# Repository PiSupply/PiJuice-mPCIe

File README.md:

# PiJuice-mPCIe
Resources for the PiJuice mPCIe board

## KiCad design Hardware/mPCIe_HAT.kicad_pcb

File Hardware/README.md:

# Hardware

EC25 datasheets - https://www.quectel.com/ProductDownload/EC25MiniPCIe.html

Change Log:

- V1.1_2021_12_30
    - Q2B connection fix
    - Position file generated

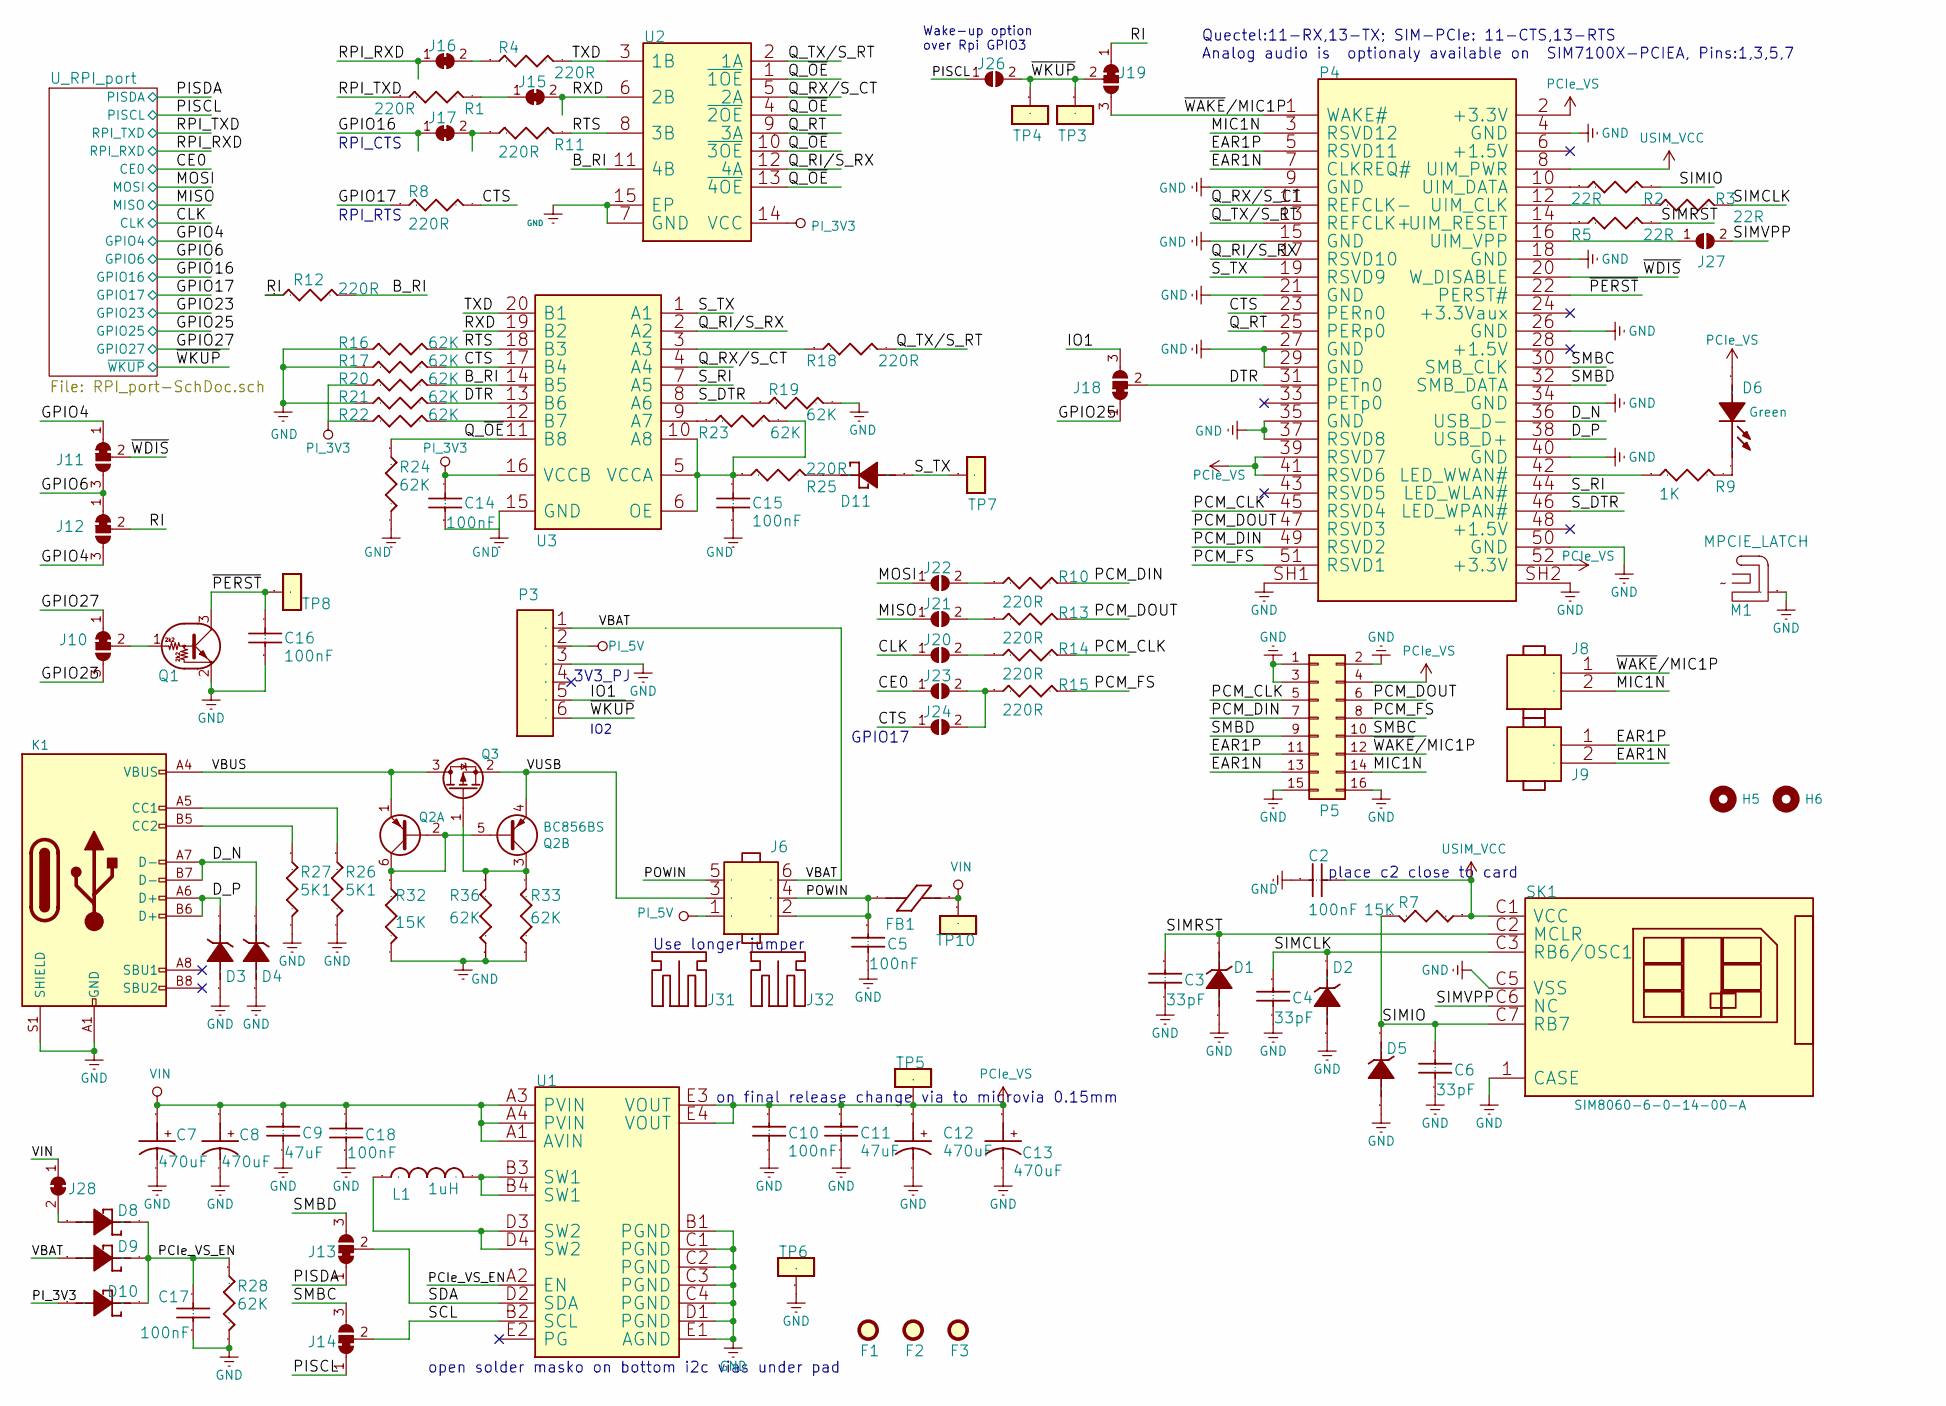
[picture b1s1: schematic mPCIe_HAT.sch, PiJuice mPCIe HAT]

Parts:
C2, C5, C10, C14, C15, C16, C17, C18: 100nF; C_0402_1005Metric; Part Number GRM155R61E104KA87D
C3, C4, C6: 33pF; C_0402_1005Metric; Part Number CC0402JRNP09BN330
C7, C8, C12, C13: 470uF; C_Elec_6.3x7.7; Part Number EEEFTA471XAP
C9, C11: 47uF; C_0805_2012Metric; Part Number GRM21BR61A476ME15L
D1, D2, D3, D4, D5: DIODFN2_98X58X50L26X51N; Part Number SP3030-01ETG
D6: Green; LED_0402_1005Metric; Part Number APG1005VGC-T-5MAV
D8, D9, D10, D11: SODFL1006X40N; Part Number NSR0240P2T5G
F1, F2, F3: Fiducial_1.5mm_Mask3mm
FB1: FBD_1206_3216Metric; Part Number FBMJ3216HS480NT
H5, H6: MountingHole; MountingHole_2.1mm
J6: PinHeader_2x03_P2.54mm_Horizontal_SMD; Part Number 11144
J8, J9: PinHeader_1x02_P1.27mm_Vertical
J10, J11, J12, J13, J14, J18, J19: SolderJumper-3_P1.3mm_Bridged12_Pad1x2.2mm_NumberLabels
J15, J16, J17, J28: SolderJumper-2_P1.3mm_Bridged_Pad1.0x1.5mm
J20, J21, J22, J23, J24, J26, J27: SolderJumper-2_P1.3mm_Open_Pad1.0x1.5mm
J31, J32: ShortingJumperCapHorizontal-2_P2.54mm; Part Number SNT-100-BK-G
K1: USB_C_Receptacle_USB2.0; USB_C_Receptacle_GCT_USB4105-GF-A; Part Number TYPE-C.16PIN.040
L1: 1uH; L_Murata_DFE2016; Part Number DFE201612E-1R0M
M1: MPCIE_LATCH; MPCIE_LATCH_0480994000; Part Number 0480994000
P3: CONN_1X6_SMT_Through_Board; Part Number BG125-06-A-1-1-0440-N-C
P4: TE_1775838-2; Part Number 1775838-2
P5: DF40C-12DP-0.4V-51; Part Number DF40C-12DP-0.4V(51)
Q1: SOT-723; Part Number DTC023EMT2L
Q2: BC856BS; SOT-363_SC-70-6; Part Number BC856S
Q3: DMP3013SFV; SOT-23; Part Number DMP2035U-7
R1, R4, R8, R10, R11, R12, R13, R14, R15, R18, R25: 220R; R_0402_1005Metric; Part Number ERJ2RKF2200X
R2, R3, R5: 22R; R_0402_1005Metric; Part Number RC0402FR-0722RL
R7, R32: 15K; R_0402_1005Metric; Part Number RC0402JR-0715KL
R9: 1K; R_0402_1005Metric; Part Number RT0402FRE071KL
R16, R17, R19, R20, R21, R22, R23, R24, R28, R33, R36: 62K; R_0402_1005Metric; Part Number RC0402FR-0762KL
R26, R27: 5K1; R_0402_1005Metric; Part Number RC0402FR-075K1L
SK1: NANO_SIM8060-6-0-14-00-A; Part Number SIM8060-6-0-14-00-A
TP3, TP4, TP5, TP6, TP7, TP10: TestPoint_THTPad_D1.1mm_Drill0.55mm
TP8: TestPoint_Pad_D1.0mm
U1: BGA20N40P4X5_199X194X60N; Part Number FAN49103AUC340X
U2: DHVQFN14-2.5x3.kicad_mod; Part Number 74CBTLV3125BQ,115
U3: USON-20_2x4mm_P0.4mm; Part Number TXB0108DQSR

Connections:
/B_RI: R12.2, R20.2, U2.11 (4B), U3.14 (B5)
/CE0: J23.1 (A); also elsewhere on the board
/CLK: J20.1 (A); also elsewhere on the board
/CTS: J24.1 (A), P4.23 (PERn0), R8.2, R17.2, U3.17 (B4)
/DTR: J18.2 (C), P4.31 (PETn0), R21.2, U3.13 (B6)
/D_N: D4.2 (CATHODE), K1.A7 (D-), K1.B7 (D-), P4.36 (USB_D-)
/D_P: D3.2 (CATHODE), K1.A6 (D+), K1.B6 (D+), P4.38 (USB_D+)
/EAR1N: J9.2, P4.7 (CLKREQ#), P5.13
/EAR1P: J9.1, P4.5 (RSVD11), P5.11
/GPIO4: J11.1 (A), J12.3 (B); also elsewhere on the board
/GPIO6: J11.3 (B), J12.1 (A); also elsewhere on the board
/GPIO16: J17.1 (A); also elsewhere on the board
/GPIO17: R8.1; also elsewhere on the board
/GPIO23: J10.3 (B); also elsewhere on the board
/GPIO25: J18.1 (A); also elsewhere on the board
/GPIO27: J10.1 (A); also elsewhere on the board
/IO1: J18.3 (B), P3.5
/MIC1N: J8.2, P4.3 (RSVD12), P5.14
/MISO: J21.1 (A); also elsewhere on the board
/MOSI: J22.1 (A); also elsewhere on the board
/PCIe_VS_EN: C17.2, D8.2 (CATHODE), D9.2 (CATHODE), D10.2 (CATHODE), R28.1, U1.A2 (EN)
/PCM_CLK: P4.45 (RSVD4), P5.5, R14.2
/PCM_DIN: P4.49 (RSVD2), P5.7, R10.2
/PCM_DOUT: P4.47 (RSVD3), P5.6, R13.2
/PCM_FS: P4.51 (RSVD1), P5.8, R15.2
/PISCL: J14.1 (A), J26.1 (A); also elsewhere on the board
/PISDA: J13.1 (A); also elsewhere on the board
/POWIN: C5.1, FB1.2, J6.2, J6.4, J6.5
/Q_RI/S_RX: P4.17 (RSVD10), U2.12 (4A), U3.2 (A2)
/Q_RT: P4.25 (PERp0), U2.9 (3A)
/Q_RX/S_CT: P4.11 (REFCLK-), U2.5 (2A), U3.4 (A4)
/Q_TX/S_RT: P4.13 (REFCLK+), R18.2, U2.2 (1A)
/Q_~OE~: R24.1, U2.1 (~1OE), U2.4 (~2OE), U2.10 (~3OE), U2.13 (~4OE), U3.11 (B8)
/RI: J12.2 (C), J19.1 (A), R12.1
/RPI_RXD: J16.1 (A); also elsewhere on the board
/RPI_TXD: R1.1; also elsewhere on the board
/RTS: R11.2, R16.2, U2.8 (3B), U3.18 (B3)
/RXD: J15.2 (B), U2.6 (2B), U3.19 (B2)
/SCL: J14.2 (C), U1.B2 (SCL)
/SDA: J13.2 (C), U1.D2 (SDA)
/SIMCLK: C4.1, D2.2 (CATHODE), R3.2, SK1.C3 (RB6/OSC1)
/SIMIO: C6.1, D5.2 (CATHODE), R2.2, R7.2, SK1.C7 (RB7)
/SIMRST: C3.1, D1.2 (CATHODE), R5.2, SK1.C2 (MCLR)
/SIMVPP: J27.2 (B), SK1.C6 (NC)
/SMBC: J14.3 (B), P4.30 (SMB_CLK), P5.10
/SMBD: J13.3 (B), P4.32 (SMB_DATA), P5.9
/S_DTR: P4.46 (LED_WPAN#), R19.1, U3.8 (A6)
/S_RI: P4.44 (LED_WLAN#), U3.7 (A5)
/S_TX: D11.1 (ANODE), P4.19 (RSVD9), TP7.1, U3.1 (A1)
/TXD: R4.2, U2.3 (1B), U3.20 (B1)
/VBAT: D9.1 (ANODE), J6.6, P3.1
/VBUS: K1.A4 (VBUS), K1.A9 (VBUS), K1.B4 (VBUS), K1.B9 (VBUS), Q2.1 (E1), Q3.3 (D)
/VUSB: J6.3, Q2.4 (E2), Q3.2 (S)
/~PERST~: C16.2, P4.22 (PERST#), Q1.3 (C), TP8.1
/~WAKE~/MIC1P: J8.1, J19.3 (B), P4.1 (WAKE#), P5.12
/~WDIS~: J11.2 (C), P4.20 (W_DISABLE)
/~WKUP~: J19.2 (C), J26.2 (B), P3.6, TP3.1, TP4.1; also elsewhere on the board
GND: C2.1, C3.2, C4.2, C5.2, C6.2, C7.2, C8.2, C9.2, C10.2, C11.2, C12.2, C13.2, C14.1, C15.1, C16.1, C17.1, C18.1, D1.1 (ANODE), D2.1 (ANODE), D3.1 (ANODE), D4.1 (ANODE), D5.1 (ANODE), K1.A1 (GND), K1.A12 (GND), K1.B1 (GND), K1.B12 (GND), K1.S1 (SHIELD), M1.1, P3.3, P4.4 (GND), P4.9 (GND), P4.15 (GND), P4.18 (GND), P4.21 (GND), P4.26 (GND), P4.27 (GND), P4.29 (GND), P4.34 (GND), P4.35 (GND), P4.37 (RSVD8), P4.40 (GND), P4.50 (GND), P4.SH1, P4.SH2, P5.1, P5.2, P5.3, P5.15, P5.16, Q1.2 (E), R16.1, R17.1, R19.2, R21.1, R24.2, R26.2, R27.2, R28.2, R32.2, R33.1, R36.1, SK1.1 (CASE), SK1.C5 (VSS), TP6.1, U1.B1 (PGND), U1.C1 (PGND), U1.C2 (PGND), U1.C3 (PGND), U1.C4 (PGND), U1.D1 (PGND), U1.E1 (AGND), U2.7 (GND), U2.15 (EP), U3.15 (GND); also elsewhere on the board
unnamed: C15.2, R23.2, R25.1, U3.5 (VCCA), U3.6 (OE), U3.10 (A8)
unnamed: D6.2 (CATHODE), R9.2
unnamed: D8.1 (ANODE), J28.2 (B)
unnamed: D11.2 (CATHODE), R25.2
unnamed: J10.2 (C), Q1.1 (B)
unnamed: J15.1 (A), R1.2
unnamed: J16.2 (B), R4.1
unnamed: J17.2 (B), R11.1
unnamed: J20.2 (B), R14.1
unnamed: J21.2 (B), R13.1
unnamed: J22.2 (B), R10.1
unnamed: J23.2 (B), J24.2 (B), R15.1
unnamed: J27.1 (A), P4.16 (UIM_VPP)
unnamed: K1.A5 (CC1), R26.1
unnamed: K1.B5 (CC2), R27.1
unnamed: L1.1, U1.D3 (SW2), U1.D4 (SW2)
unnamed: L1.2, U1.B3 (SW1), U1.B4 (SW1)
unnamed: P4.10 (UIM_DATA), R2.1
unnamed: P4.12 (UIM_CLK), R3.1
unnamed: P4.14 (UIM_RESET), R5.1
unnamed: P4.42 (LED_WWAN#), R9.1
unnamed: Q2.2 (B1), Q2.5 (B2), Q2.6 (C1), R32.1
unnamed: Q2.3 (C2), Q3.1 (G), R33.2, R36.2
unnamed: R18.1, U3.3 (A3)
unnamed: R22.2, U3.12 (B7)
unnamed: R23.1, U3.9 (A7)
PCIe_VS: C10.1, C11.1, C12.1, C13.1, D6.1 (ANODE), P4.2 (+3.3V), P4.39 (RSVD7), P4.41 (RSVD6), P4.52 (+3.3V), P5.4, TP5.1, U1.E3 (VOUT), U1.E4 (VOUT)
PI_3V3: C14.2, D10.1 (ANODE), R20.1, R22.1, U2.14 (VCC), U3.16 (VCCB); also elsewhere on the board
PI_5V: J6.1, P3.2; also elsewhere on the board
USIM_VCC: C2.2, P4.8 (UIM_PWR), R7.1, SK1.C1 (VCC)
VIN: C7.1, C8.1, C9.1, C18.2, FB1.1, J28.1 (A), TP10.1, U1.A1 (AVIN), U1.A3 (PVIN), U1.A4 (PVIN)

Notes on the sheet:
Analog audio is optionaly available on SIM7100X-PCIEA, Pins:1,3,5,7
Quectel:11-RX,13-TX; SIM-PCIe: 11-CTS,13-RTS
on final release change via to microvia 0.15mm
open solder masko on bottom i2c vias under pad
place c2 close to card
RPI_RTS
RPI_CTS
Wake-up option over Rpi GPIO3
GPIO17
IO2
3V3_PJ
Use longer jumper

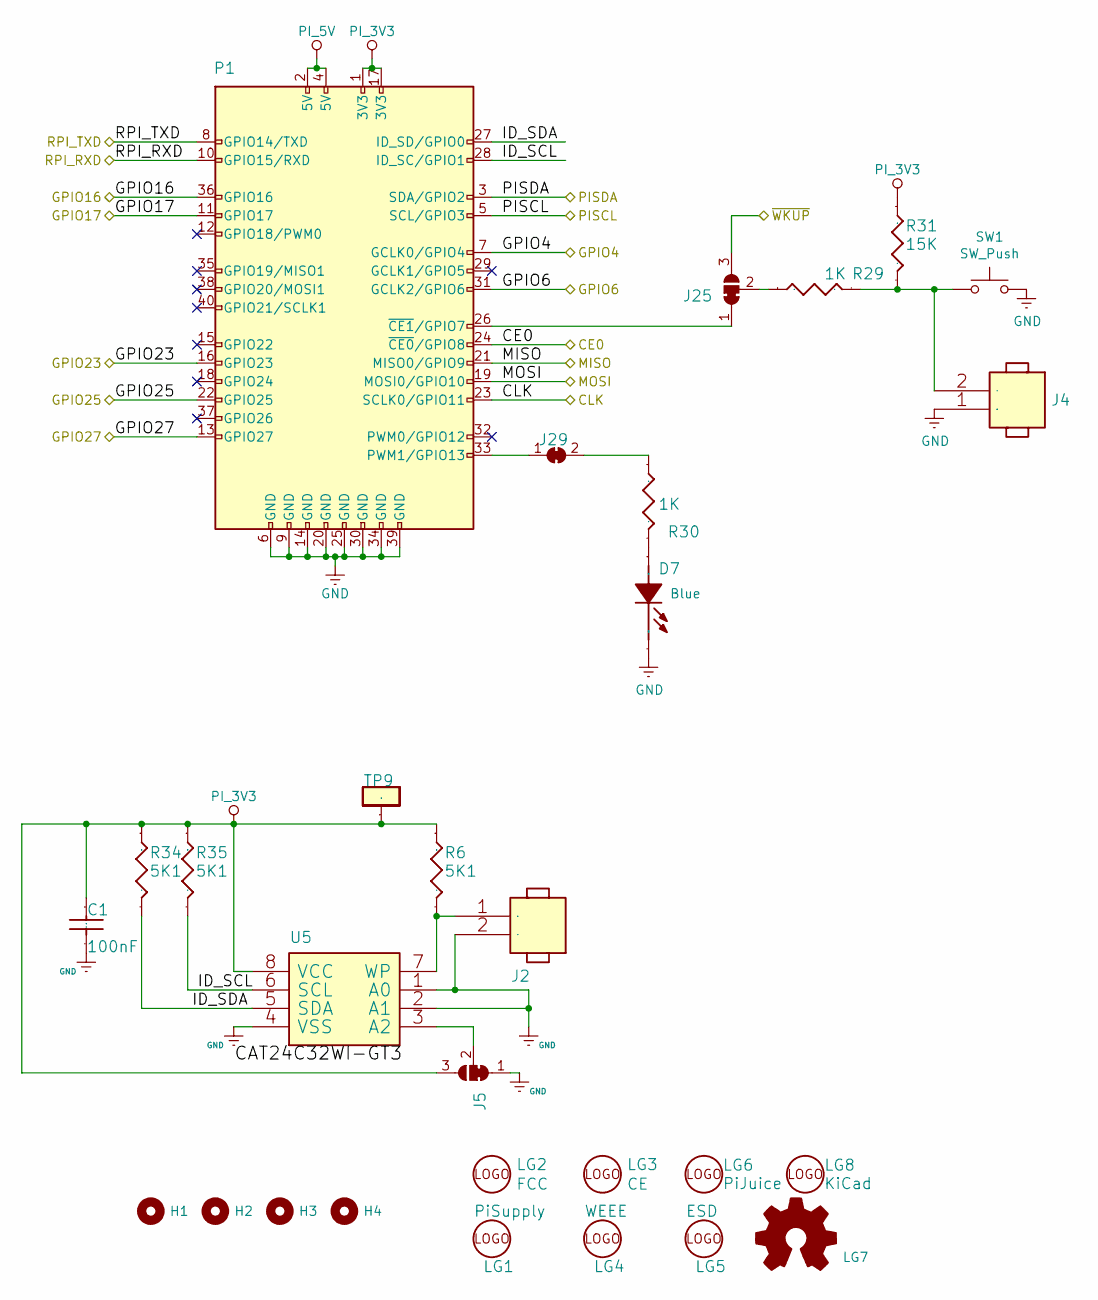
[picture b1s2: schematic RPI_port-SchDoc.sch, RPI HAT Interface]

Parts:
C1: 100nF; C_0402_1005Metric; Part Number GRM155R61E104KA87D
D7: Blue; LED_0402_1005Metric; Part Number APG1005PBC-T-5MAV
H1, H2, H3, H4: MountingHole; MountingHole_RPI_2.7mm_M2.5
J2: PinHeader_1x02_P1.27mm_Vertical
J4: EMCON_HEADER_1x2-; PinHeader_1x02_P2.54mm_Vertical
J5, J25: jumper; SolderJumper-3_P1.3mm_Bridged12_Pad1x2.2mm_NumberLabels
J29: SolderJumper-2_P1.3mm_Bridged_Pad1.0x1.5mm
LG1: PiSupply
LG2: FCC
LG3: CE
LG4: WEEE; WEEE-Logo_4.2x6mm_SilkScreen
LG5: ESD; Symbol_ESD-Logo_CopperTop
LG6: PiJuice; Pijuice
LG7: Logo_Open_Hardware_Small; oshw
LG8: KiCad
P1: EMCON_RPI_GPIO_HEADER_2x20; CONN_2X20_SMT_Through_Board; Part Number REF-182665-01
R6, R34, R35: 5K1; R_0402_1005Metric; Part Number RC0402FR-075K1L
R29, R30: 1K; R_0402_1005Metric; Part Number RT0402FRE071KL
R31: 15K; R_0402_1005Metric; Part Number RC0402JR-0715KL
SW1: SW_Push; SW_TACT_6X3; Part Number TL3302AF180QJ
TP9: TestPoint_Pad_D1.0mm
U5: SOIC-8_3.9x4.9mm_P1.27mm; Part Number CAT24C32WI-GT3

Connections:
/CE0: P1.24 (~CE0~/GPIO8); also elsewhere on the board
/CLK: P1.23 (SCLK0/GPIO11); also elsewhere on the board
/GPIO4: P1.7 (GCLK0/GPIO4); also elsewhere on the board
/GPIO6: P1.31 (GCLK2/GPIO6); also elsewhere on the board
/GPIO16: P1.36 (GPIO16); also elsewhere on the board
/GPIO17: P1.11 (GPIO17); also elsewhere on the board
/GPIO23: P1.16 (GPIO23); also elsewhere on the board
/GPIO25: P1.22 (GPIO25); also elsewhere on the board
/GPIO27: P1.13 (GPIO27); also elsewhere on the board
/MISO: P1.21 (MISO0/GPIO9); also elsewhere on the board
/MOSI: P1.19 (MOSI0/GPIO10); also elsewhere on the board
/PISCL: P1.5 (SCL/GPIO3); also elsewhere on the board
/PISDA: P1.3 (SDA/GPIO2); also elsewhere on the board
/RPI_RXD: P1.10 (GPIO15/RXD); also elsewhere on the board
/RPI_TXD: P1.8 (GPIO14/TXD); also elsewhere on the board
/U_RPI_port/ID_SCL: P1.28 (ID_SC/GPIO1), R35.2, U5.6 (SCL)
/U_RPI_port/ID_SDA: P1.27 (ID_SD/GPIO0), R34.2, U5.5 (SDA)
/~WKUP~: J25.3 (B); also elsewhere on the board
GND: C1.2, D7.2 (CATHODE), J2.2, J4.1, J5.1 (A), P1.6 (GND), P1.9 (GND), P1.14 (GND), P1.20 (GND), P1.25 (GND), P1.30 (GND), P1.34 (GND), P1.39 (GND), SW1.2, U5.1 (A0), U5.2 (A1), U5.4 (VSS); also elsewhere on the board
unnamed: D7.1 (ANODE), R30.2
unnamed: J2.1, R6.2, U5.7 (WP)
unnamed: J4.2, R29.2, R31.2, SW1.1
unnamed: J5.2 (C), U5.3 (A2)
unnamed: J25.1 (A), P1.26 (~CE1~/GPIO7)
unnamed: J25.2 (C), R29.1
unnamed: J29.1 (A), P1.33 (PWM1/GPIO13)
unnamed: J29.2 (B), R30.1
PI_3V3: C1.1, J5.3 (B), P1.1 (3V3), P1.17 (3V3), R6.1, R31.1, R34.1, R35.1, TP9.1, U5.8 (VCC); also elsewhere on the board
PI_5V: P1.2 (5V), P1.4 (5V); also elsewhere on the board

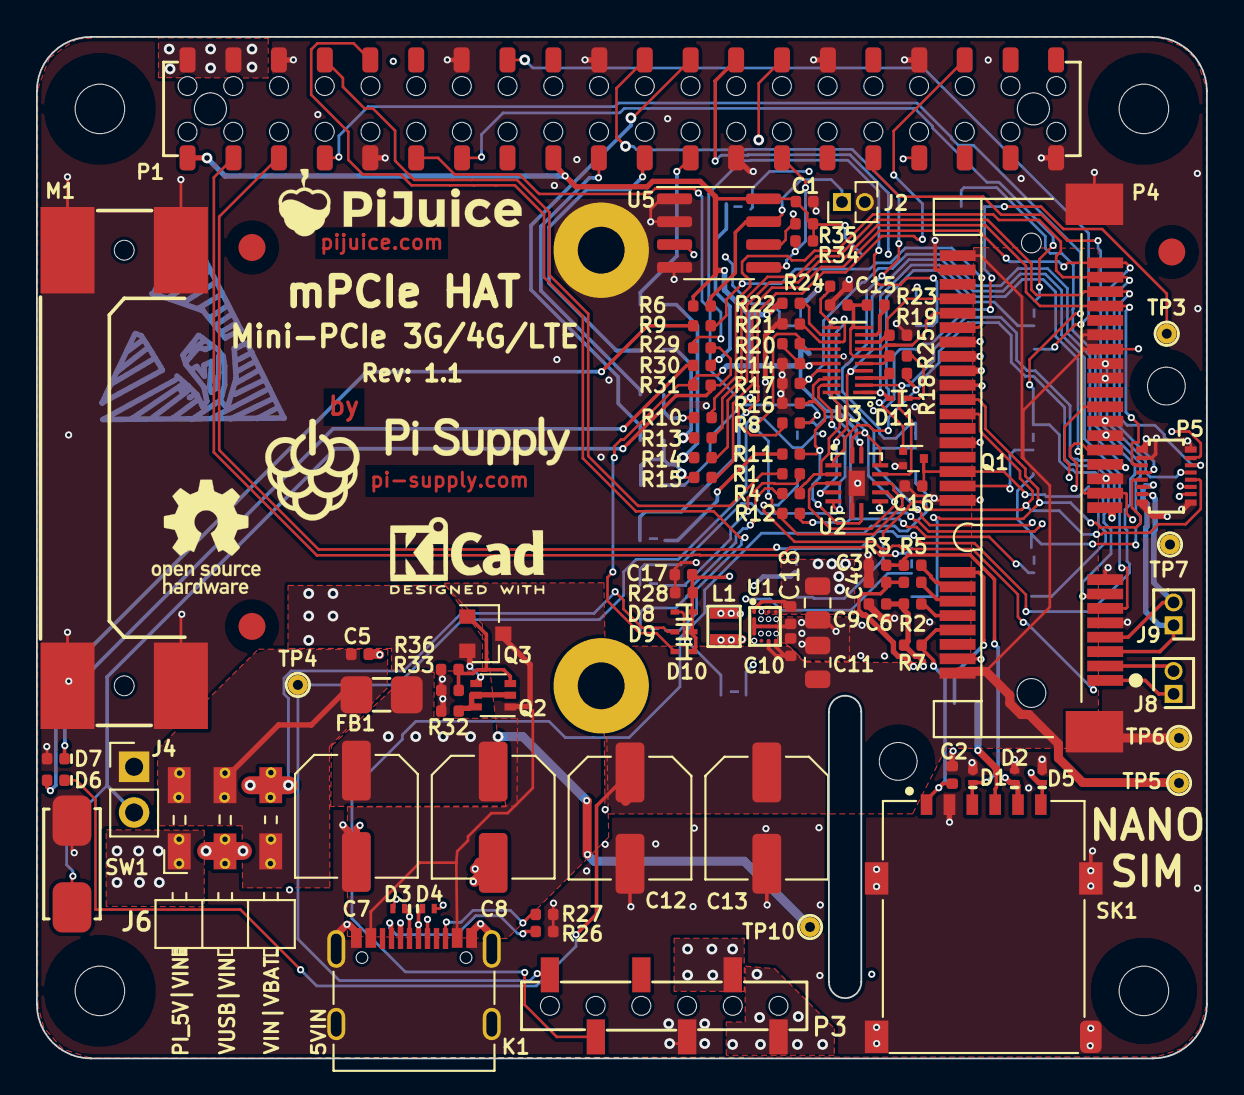
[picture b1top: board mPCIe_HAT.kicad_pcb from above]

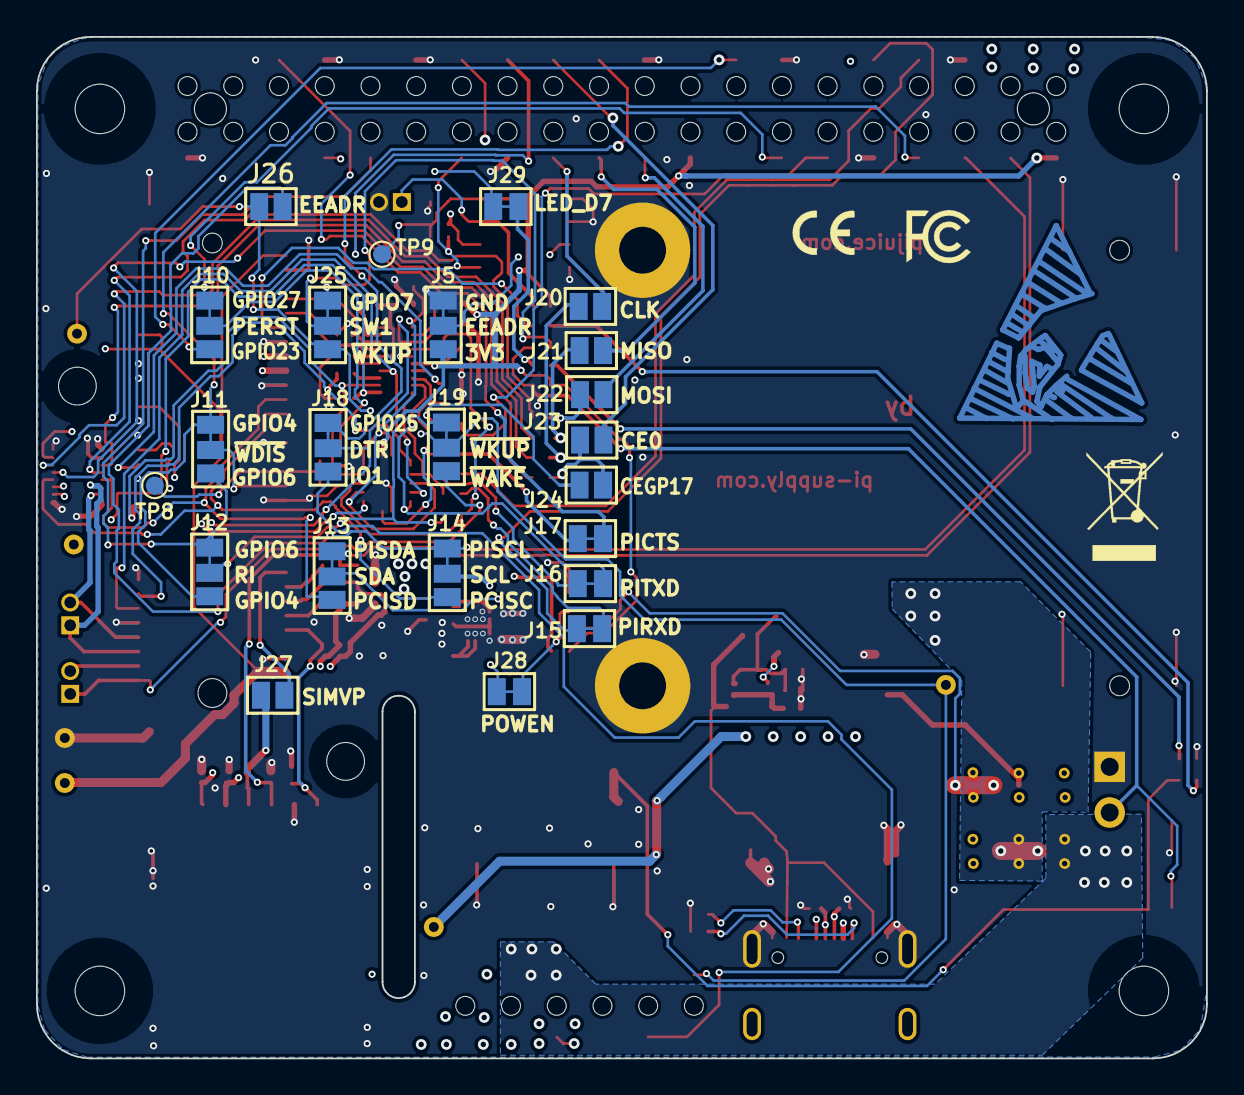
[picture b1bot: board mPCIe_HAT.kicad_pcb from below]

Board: 4 copper layers, 65.0 x 56.8 mm, 135 parts (27 on the bottom side), 99 nets.

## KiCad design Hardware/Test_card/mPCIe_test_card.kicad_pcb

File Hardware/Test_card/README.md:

# mPCIe Test Card design 

Used for testing PiJuice mPCIe HATs

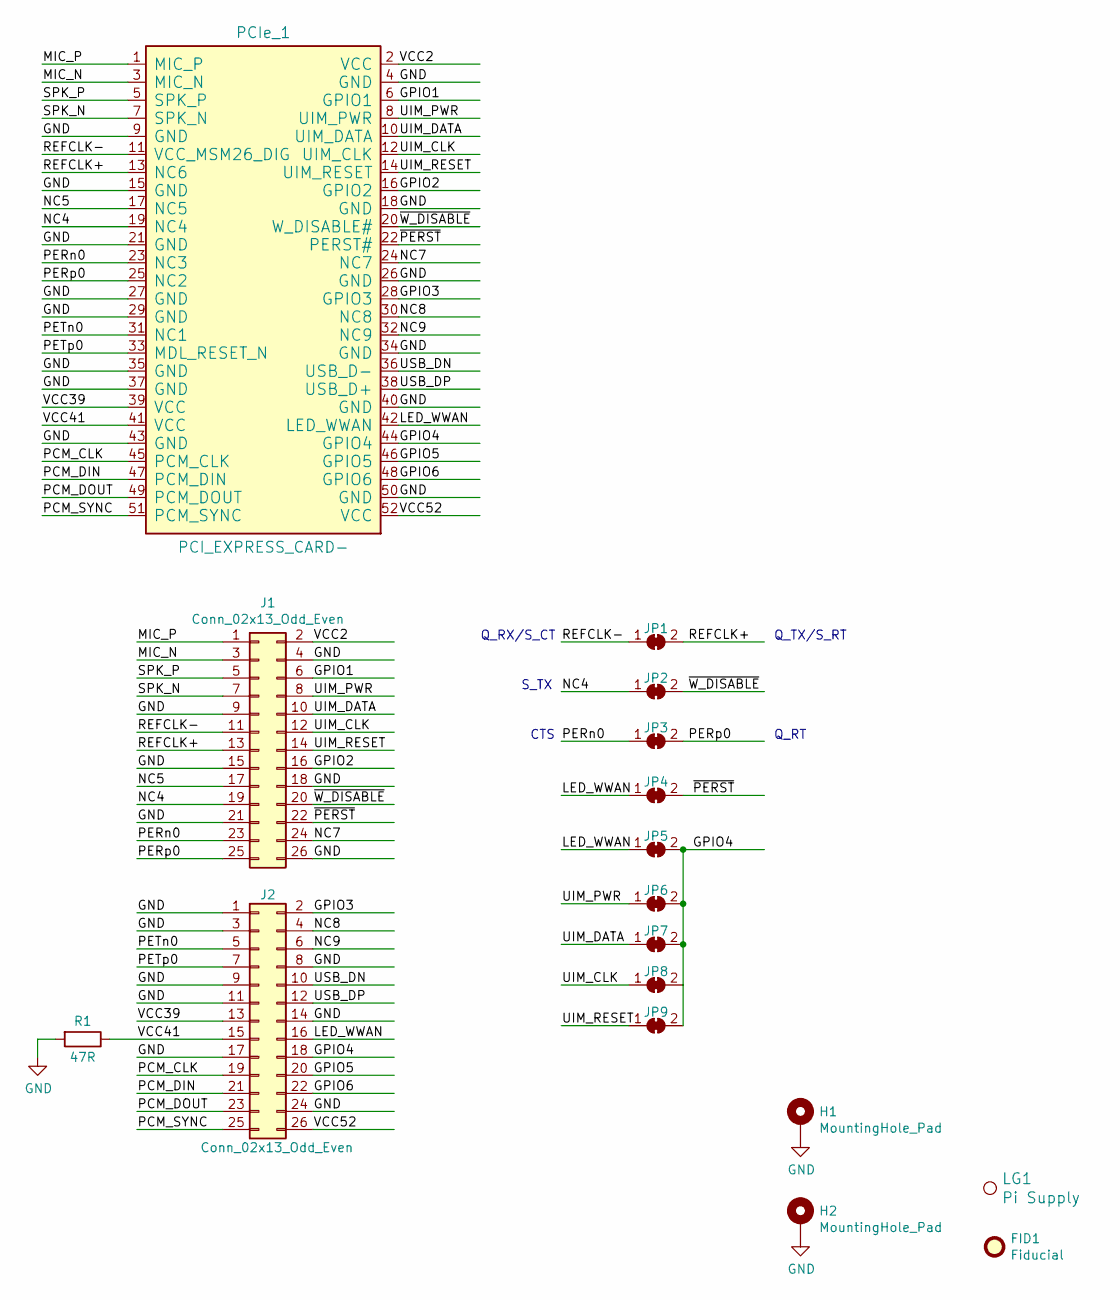
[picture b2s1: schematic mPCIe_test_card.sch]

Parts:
FID1: Fiducial; Fiducial_0.75mm_Mask1.5mm
H1, H2: MountingHole_Pad; MountingHole
J1, J2: Conn_02x13_Odd_Even; PinHeader_2x13_P2.54mm_Vertical
JP1, JP2, JP3, JP4, JP5, JP6, JP7, JP8, JP9: SolderJumper_2_Bridged; SolderJumper-2_P1.3mm_Bridged
LG1: Pi Supply; PiSupply
PCIe_1: PCI_EXPRESS_CARD-; PCIeMini-GF-2D-800-1K-S52
R1: 47R; R_Axial_DIN0414_L11.9mm_D4.5mm_P15.24mm_Horizontal; Part Number KNP100FR-73-47R

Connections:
/GPIO1: J1.6, PCIe_1.6 (GPIO1)
/GPIO2: J1.16, PCIe_1.16 (GPIO2)
/GPIO3: J2.2, PCIe_1.28 (GPIO3)
/GPIO4: J2.18, JP5.2 (B), JP6.2 (B), JP7.2 (B), JP8.2 (B), JP9.2 (B), PCIe_1.44 (GPIO4)
/GPIO5: J2.20, PCIe_1.46 (GPIO5)
/GPIO6: J2.22, PCIe_1.48 (GPIO6)
/LED_WWAN: J2.16, JP4.1 (A), JP5.1 (A), PCIe_1.42 (LED_WWAN)
/MIC_N: J1.3, PCIe_1.3 (MIC_N)
/MIC_P: J1.1, PCIe_1.1 (MIC_P)
/NC4: J1.19, JP2.1 (A), PCIe_1.19 (NC4)
/NC5: J1.17, PCIe_1.17 (NC5)
/NC7: J1.24, PCIe_1.24 (NC7)
/NC8: J2.4, PCIe_1.30 (NC8)
/NC9: J2.6, PCIe_1.32 (NC9)
/PCM_CLK: J2.19, PCIe_1.45 (PCM_CLK)
/PCM_DIN: J2.21, PCIe_1.47 (PCM_DIN)
/PCM_DOUT: J2.23, PCIe_1.49 (PCM_DOUT)
/PCM_SYNC: J2.25, PCIe_1.51 (PCM_SYNC)
/PERn0: J1.23, JP3.1 (A), PCIe_1.23 (NC3)
/PERp0: J1.25, JP3.2 (B), PCIe_1.25 (NC2)
/PETn0: J2.5, PCIe_1.31 (NC1)
/PETp0: J2.7, PCIe_1.33 (MDL_RESET_N)
/REFCLK+: J1.13, JP1.2 (B), PCIe_1.13 (NC6)
/REFCLK-: J1.11, JP1.1 (A), PCIe_1.11 (VCC_MSM26_DIG)
/SPK_N: J1.7, PCIe_1.7 (SPK_N)
/SPK_P: J1.5, PCIe_1.5 (SPK_P)
/UIM_CLK: J1.12, JP8.1 (A), PCIe_1.12 (UIM_CLK)
/UIM_DATA: J1.10, JP7.1 (A), PCIe_1.10 (UIM_DATA)
/UIM_PWR: J1.8, JP6.1 (A), PCIe_1.8 (UIM_PWR)
/UIM_RESET: J1.14, JP9.1 (A), PCIe_1.14 (UIM_RESET)
/USB_DN: J2.10, PCIe_1.36 (USB_D-)
/USB_DP: J2.12, PCIe_1.38 (USB_D+)
/VCC2: J1.2, PCIe_1.2 (VCC)
/VCC39: J2.13, PCIe_1.39 (VCC)
/VCC41: J2.15, PCIe_1.41 (VCC), R1.1
/VCC52: J2.26, PCIe_1.52 (VCC)
/~PERST~: J1.22, JP4.2 (B), PCIe_1.22 (PERST#)
/~W_DISABLE~: J1.20, JP2.2 (B), PCIe_1.20 (W_DISABLE#)
GND: H1.1, H2.1, J1.4, J1.9, J1.15, J1.18, J1.21, J1.26, J2.1, J2.3, J2.8, J2.9, J2.11, J2.14, J2.17, J2.24, PCIe_1.4 (GND), PCIe_1.9 (GND), PCIe_1.15 (GND), PCIe_1.18 (GND), PCIe_1.21 (GND), PCIe_1.26 (GND), PCIe_1.27 (GND), PCIe_1.29 (GND), PCIe_1.34 (GND), PCIe_1.35 (GND), PCIe_1.37 (GND), PCIe_1.40 (GND), PCIe_1.43 (GND), PCIe_1.50 (GND), R1.2

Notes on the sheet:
CTS
Q_RT
S_TX
Q_RX/S_CT
Q_TX/S_RT

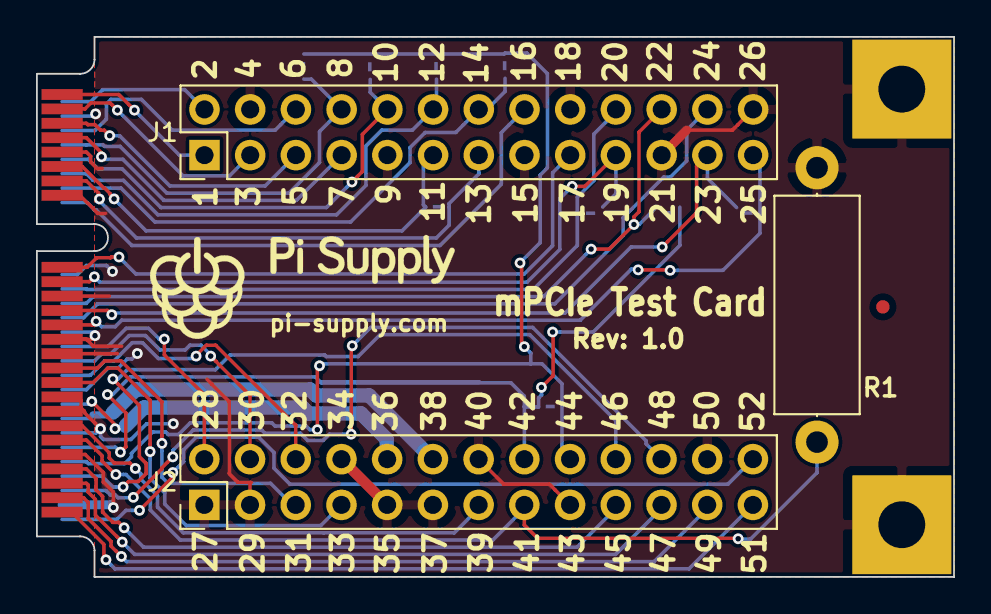
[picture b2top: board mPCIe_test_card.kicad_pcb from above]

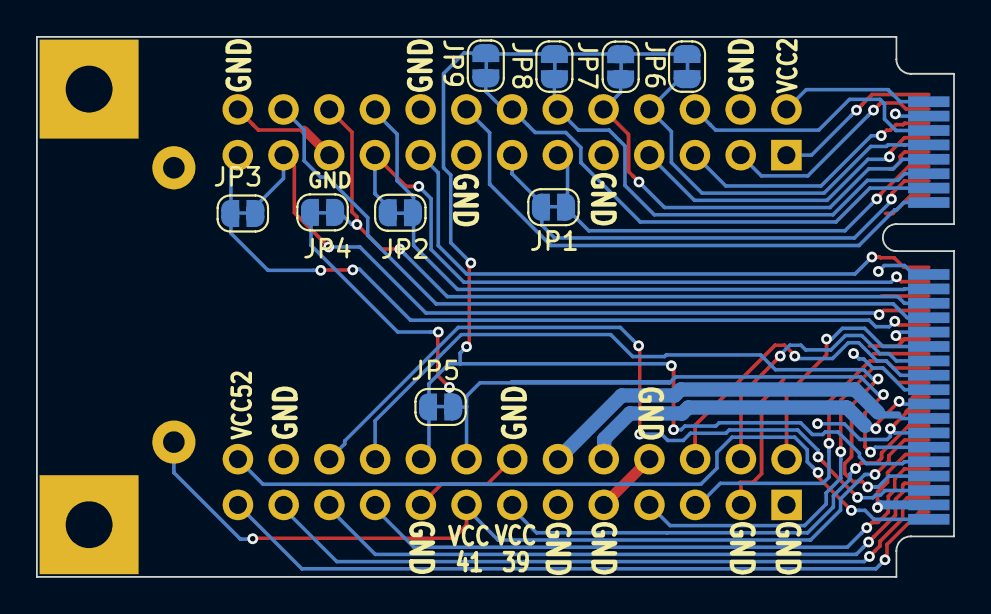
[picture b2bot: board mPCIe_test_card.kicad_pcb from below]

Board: 2 copper layers, 50.9 x 30.0 mm, 17 parts (9 on the bottom side), 39 nets.

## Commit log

2018-11-23 init
    init
2018-11-23 ec25 datasheet link
    ec25
2018-11-23 add quectel datasheets
    add quectel datasheets
2021-02-25 Added interactive BOM
2021-02-25 Top Side Render
2021-02-25 PCB Library Created
2021-02-25 Added PCB Library footprints
2021-02-25 Create LICENSE
2021-05-11 Initial Design Rev 1.0
2021-12-30 Q2B connection fix, position file generated.
